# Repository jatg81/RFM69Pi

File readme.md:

# Programmer_ArduinoISP

This is a modification of the RFM69Pi developed for https://wiki.openenergymonitor.org/index.php/RFM69Pi_V3

Improvements:

- Added uFL connector to board for using external antena
- Smaller size

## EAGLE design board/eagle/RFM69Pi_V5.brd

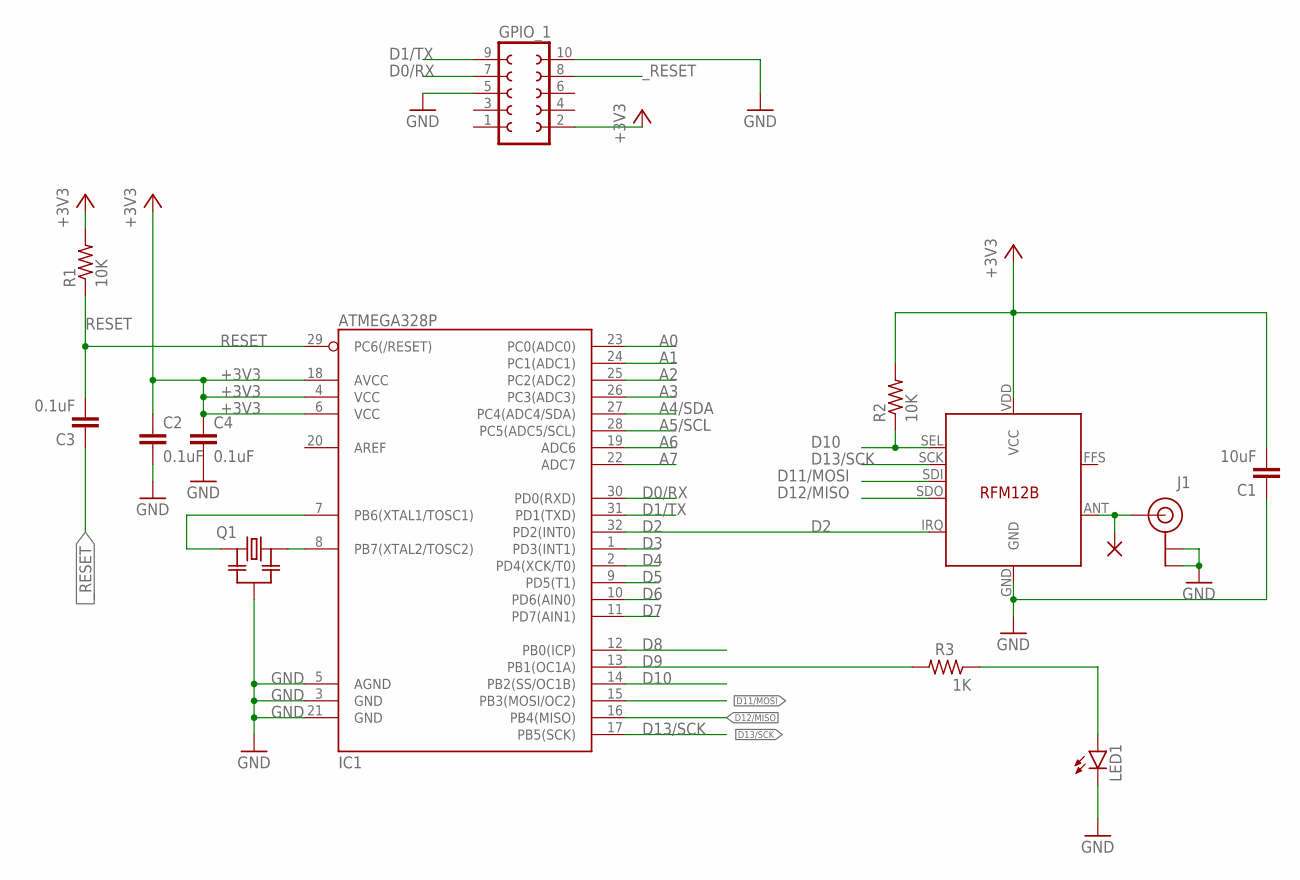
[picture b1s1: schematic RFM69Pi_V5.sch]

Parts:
C1: 10uF; C0603
C2, C3, C4: 0.1uF; C0603
GPIO_1: CON-LSTA_FE05-2
IC1: ATMEGA328P; TQFP32-08
J1: U.FL
LED1: LEDSML0603; SML0603
PAD2: 1,6/0,8
Q1: RESONATOR-MURATACST_CE; RESONATOR_MURATA2
R1, R2: 10K; R0603
R3: 1K; R0603
RFM69CW: RFM69CW; RFM12B

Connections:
+3V3: C1.2, C2.1, C4.1, GPIO_1.2, IC1.4 (VCC), IC1.6 (VCC), IC1.18 (AVCC), R1.2, R2.2, RFM69CW.VDD (VCC)
A0: IC1.23 (PC0(ADC0))
A1: IC1.24 (PC1(ADC1))
A2: IC1.25 (PC2(ADC2))
A3: IC1.26 (PC3(ADC3))
A4/SDA: IC1.27 (PC4(ADC4/SDA))
A5/SCL: IC1.28 (PC5(ADC5/SCL))
A6: IC1.19 (ADC6)
A7: IC1.22 (ADC7)
D0/RX: GPIO_1.7, IC1.30 (PD0(RXD))
D1/TX: GPIO_1.9, IC1.31 (PD1(TXD))
D2: IC1.32 (PD2(INT0)), RFM69CW.IRQ
D3: IC1.1 (PD3(INT1))
D4: IC1.2 (PD4(XCK/T0))
D5: IC1.9 (PD5(T1))
D6: IC1.10 (PD6(AIN0))
D7: IC1.11 (PD7(AIN1))
D8: IC1.12 (PB0(ICP))
D9: IC1.13 (PB1(OC1A)), R3.2
D10: IC1.14 (PB2(SS/OC1B)), R2.1, RFM69CW.SEL
D11/MOSI: IC1.15 (PB3(MOSI/OC2)), RFM69CW.SDI
D12/MISO: IC1.16 (PB4(MISO)), RFM69CW.SDO
D13/SCK: IC1.17 (PB5(SCK)), RFM69CW.SCK
GND: C1.1, C2.2, C4.2, GPIO_1.5, GPIO_1.10, IC1.3 (GND), IC1.5 (AGND), IC1.21 (GND), J1.1 (GND), J1.2 (GND), LED1.C, Q1.2, RFM69CW.GND
unnamed: IC1.7 (PB6(XTAL1/TOSC1)), Q1.1
unnamed: IC1.8 (PB7(XTAL2/TOSC2)), Q1.3
unnamed: LED1.A, R3.1
unnamed: J1.FEED (SIGNAL), PAD2.1, RFM69CW.ANT
RESET: C3.2, IC1.29 (PC6(/RESET)), R1.1
_RESET: C3.1, GPIO_1.8

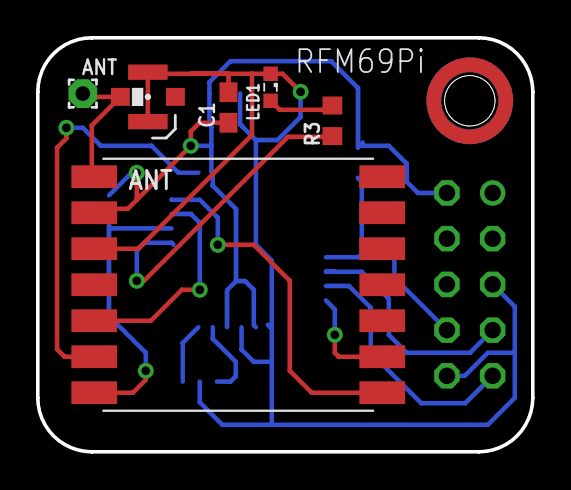
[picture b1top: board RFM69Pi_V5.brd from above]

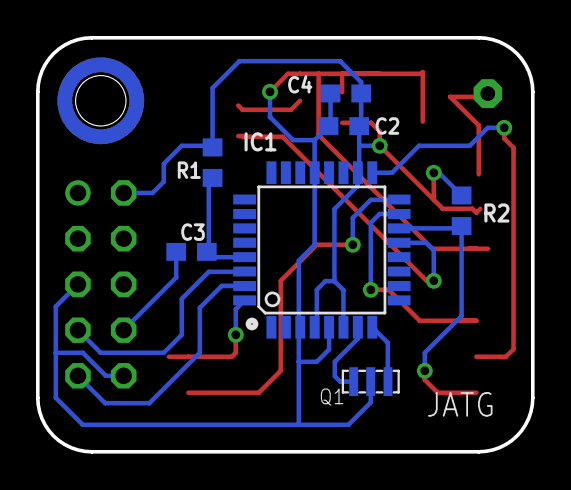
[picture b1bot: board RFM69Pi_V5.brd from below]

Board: 2 copper layers, 27.5 x 23.0 mm, 14 parts (7 on the bottom side), 16 nets.

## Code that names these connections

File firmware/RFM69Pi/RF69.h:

#include <avr/interrupt.h>
#include <util/crc16.h>
#define __PROG_TYPES_COMPAT__
#include <avr/pgmspace.h>

#define REG_FIFO            0x00
#define REG_OPMODE          0x01
#define REG_FRFMSB          0x07
#define REG_AFCFEI          0x1E
#define REG_RSSIVALUE       0x24
#define REG_DIOMAPPING1     0x25
#define REG_IRQFLAGS1       0x27
#define REG_IRQFLAGS2       0x28
#define REG_SYNCCONFIG      0x2E
#define REG_SYNCVALUE1      0x2F
#define REG_SYNCVALUE2      0x30
#define REG_SYNCVALUE3      0x31
#define REG_NODEADRS        0x39
#define REG_PACKETCONFIG2   0x3D
#define REG_AESKEY1         0x3E
#define MODE_SLEEP          0x00
#define MODE_STANDBY        0x04
#define MODE_RECEIVER       0x10
#define MODE_TRANSMITTER    0x0C
#define IRQ1_MODEREADY      0x80
#define IRQ1_RXREADY        0x40
#define IRQ2_FIFOFULL       0x80
#define IRQ2_FIFONOTEMPTY   0x40
#define IRQ2_FIFOOVERRUN    0x10
#define IRQ2_PACKETSENT     0x08
#define IRQ2_PAYLOADREADY   0x04
#define DMAP1_PACKETSENT    0x00
#define DMAP1_PAYLOADREADY  0x40
#define DMAP1_SYNCADDRESS   0x80
#define AFC_CLEAR           0x02
#define RF_MAX                72

#define ROM_UINT8       const prog_uint8_t
#define ROM_READ_UINT8  pgm_read_byte
#define ROM_DATA        PROGMEM

#define IRQ_ENABLE      sei()
#define SS_DDR           DDRB
#define SS_PORT         PORTB
#define SS_BIT              2     // for PORTB: 2 = d.10, 1 = d.9, 0 = d.8
#define SPI_SS              2     // PB2
#define SPI_MOSI            3     // PB3
#define SPI_MISO            4     // PB4
#define SPI_SCK             5     // PB5

#define rf69_grp        rf69_buf[0]
#define rf69_hdr        rf69_buf[1]
#define rf69_len        rf69_buf[2]
#define rf69_data       (rf69_buf + 3)

#define RF69_HDR_CTL    0x80
#define RF69_HDR_DST    0x40
#define RF69_HDR_ACK    0x20
#define RF69_HDR_MASK   0x1F

#define RF69_MAXDATA    66

#define RF69_433MHZ     1   ///< RFM12B 433 MHz frequency band.
#define RF69_868MHZ     2   ///< RFM12B 868 MHz frequency band.
#define RF69_915MHZ     3   ///< RFM12B 915 MHz frequency band.

#define RF69_SLEEP           0     ///< Enter sleep mode.
#define RF69_WAKEUP         -1     ///< Wake up from sleep mode.
#define CSMA_LIMIT          -90    ///< Upper RX signal sensitivity threshold in dBm for carrier sense access
#define RF69_CSMA_LIMIT_MS  1000   ///< Max time limit waiting for non carrier sensed

// EEPROM address range used by the rf69_config() code
#define RF69_EEPROM_ADDR    ((uint8_t*) 0x20)  ///< Starting offset.
#define RF69_EEPROM_SIZE    16                 ///< Number of bytes.
#define RF69_EEPROM_EKEY    ((uint8_t*) 0x40)  ///< EE start, same as before.
#define RF69_EEPROM_ELEN    16                 ///< EE number of bytes.
#define RF69_EEPROM_VERSION 1                  ///< Only this version is valid.

#define RF_SLEEP_MODE   0x8205

/// Shorthand to simplify detecting a request for an ACK.
#define RF69_WANTS_ACK ((rf69_hdr & RF69_HDR_ACK) && !(rf69_hdr & RF69_HDR_CTL))
/// Shorthand to simplify sending out the proper ACK reply.
#define RF69_ACK_REPLY (rf69_hdr & RF69_HDR_DST ? RF69_HDR_CTL : \
            RF69_HDR_CTL | RF69_HDR_DST | (rf69_hdr & RF69_HDR_MASK))

extern volatile uint16_t rf69_crc;
extern volatile uint8_t rf69_buf[];
extern uint8_t  rssi;

uint8_t control(uint8_t cmd, uint8_t val);
void setFrequency (uint32_t freq);
void configure ();
void interrupt();
int16_t readRSSI();
void sleep (bool off);
uint8_t rf69_initialize(uint8_t id, uint8_t band, uint8_t group=0xD4, uint16_t frequency=1600);
uint8_t rf69_configSilent();
void rf69_configDump();
uint8_t rf69_config(uint8_t show =1);
uint8_t rf69_recvDone(void);
uint8_t rf69_canSend(void);
void rf69_sendStart(uint8_t hdr, const void* ptr, uint8_t len);
void rf69_sendNow(uint8_t hdr, const void* ptr, uint8_t len);
void rf69_sendWait(uint8_t mode);
bool rf69_sendWithRetry (uint8_t nodeId,const void* ptr, uint8_t len,uint8_t retries=2, uint8_t retryWaitTime=40);
uint8_t rf69_receiveStart(uint8_t nodeIdSrc, const void* ptr, uint8_t len);
void rf69_sleep(char n);
void rf69_encrypt(const uint8_t*);

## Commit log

2019-12-20 Create j
2019-12-20 Create d
2019-12-20 Create f
2019-12-28 Create h
2020-06-21 Rename RFM69Pi_V5.brd to RFM69Pi.brd
2020-06-21 Rename RFM69Pi_V5.sch to RFM69Pi.sch
2020-06-21 Create c
2020-06-21 Rename RFM69Pi.ino to RF69Pi.ino
2020-06-21 Rename RF69Pi.ino to RFM69Pi.ino
2020-06-21 Rename RFM69.cpp to RF69.cpp
2020-06-22 Create b

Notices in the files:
parts and their libraries:
SparkFun-Connectors: Licensing: Creative Commons ShareAlike 4.0 International - https://creativecommons.org/licenses/by-sa/4.0
m-pad-2.1: License : GNU General Public License version 2 (see bottom)
